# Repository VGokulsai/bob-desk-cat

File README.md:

# Bob, the desk cat

## The story

Bob is a cat that I drew in my sketchbook. Further up he went into the Wispr Flow hiring challenge as the main character that introduces my portfolio for that challenge.

After the completion of the challenge I moved on to Hack Club's Fallen, which is like a hard hackathon lasting 2 months. You build the project by hand: no AI, no bot can help you. You record your time, you get your XP, and stuff like that.

## Why I'm building him

Bob, the bot named Bob, is my cat, my sketchbook inspiration. Why am I building him? The reason that I'm building Bob is that I could feel less lonely while coding and while doing things.

## What Bob can do

What Bob can do is this: he has a screen, a mic, a speaker, and 3 servos. When we touch Bob he acts like an ordinary cat. He yawns, sleeps, and wakes up. His mic, speaker, and servos are all connected.

## The board

The board that I'm using is the ESP32-S3, 73 mm x 62.5 mm, 38 parts, and USB-C. These are the parts that are going to be on the board. As for the checks there are 0 ERC errors, 0 DRC errors, and 0 unconnected things.

## The hardest part

The next little bit of a bad story is that the USB D+ wire was a really tough one. That was the only single wire that I needed to connect in the entire schematic so that I could submit. As it was the last one, when I was going to connect it, there was no way. I had to reconnect so many wires, some of which I had to, and change the schematic design, replace parts, and stuff like that. It's been a really tough one until now.

## Cost and what's next

The cost of all the parts is ₹1,600 as I'm from India. What's next is that I'm going to be submitting the online version of Bob for now: the schematic, the PCB design, the doc, and the readme. Then I have to order all the hardware parts that I need to build him so that we can move on more quickly and probably go design.

## Files

- `hardware/` KiCad schematic and PCB
- `hardware/fab/` Gerbers for JLCPCB, BOM, parts positions, schematic PDF, board renders
- `bom.csv` shopping list

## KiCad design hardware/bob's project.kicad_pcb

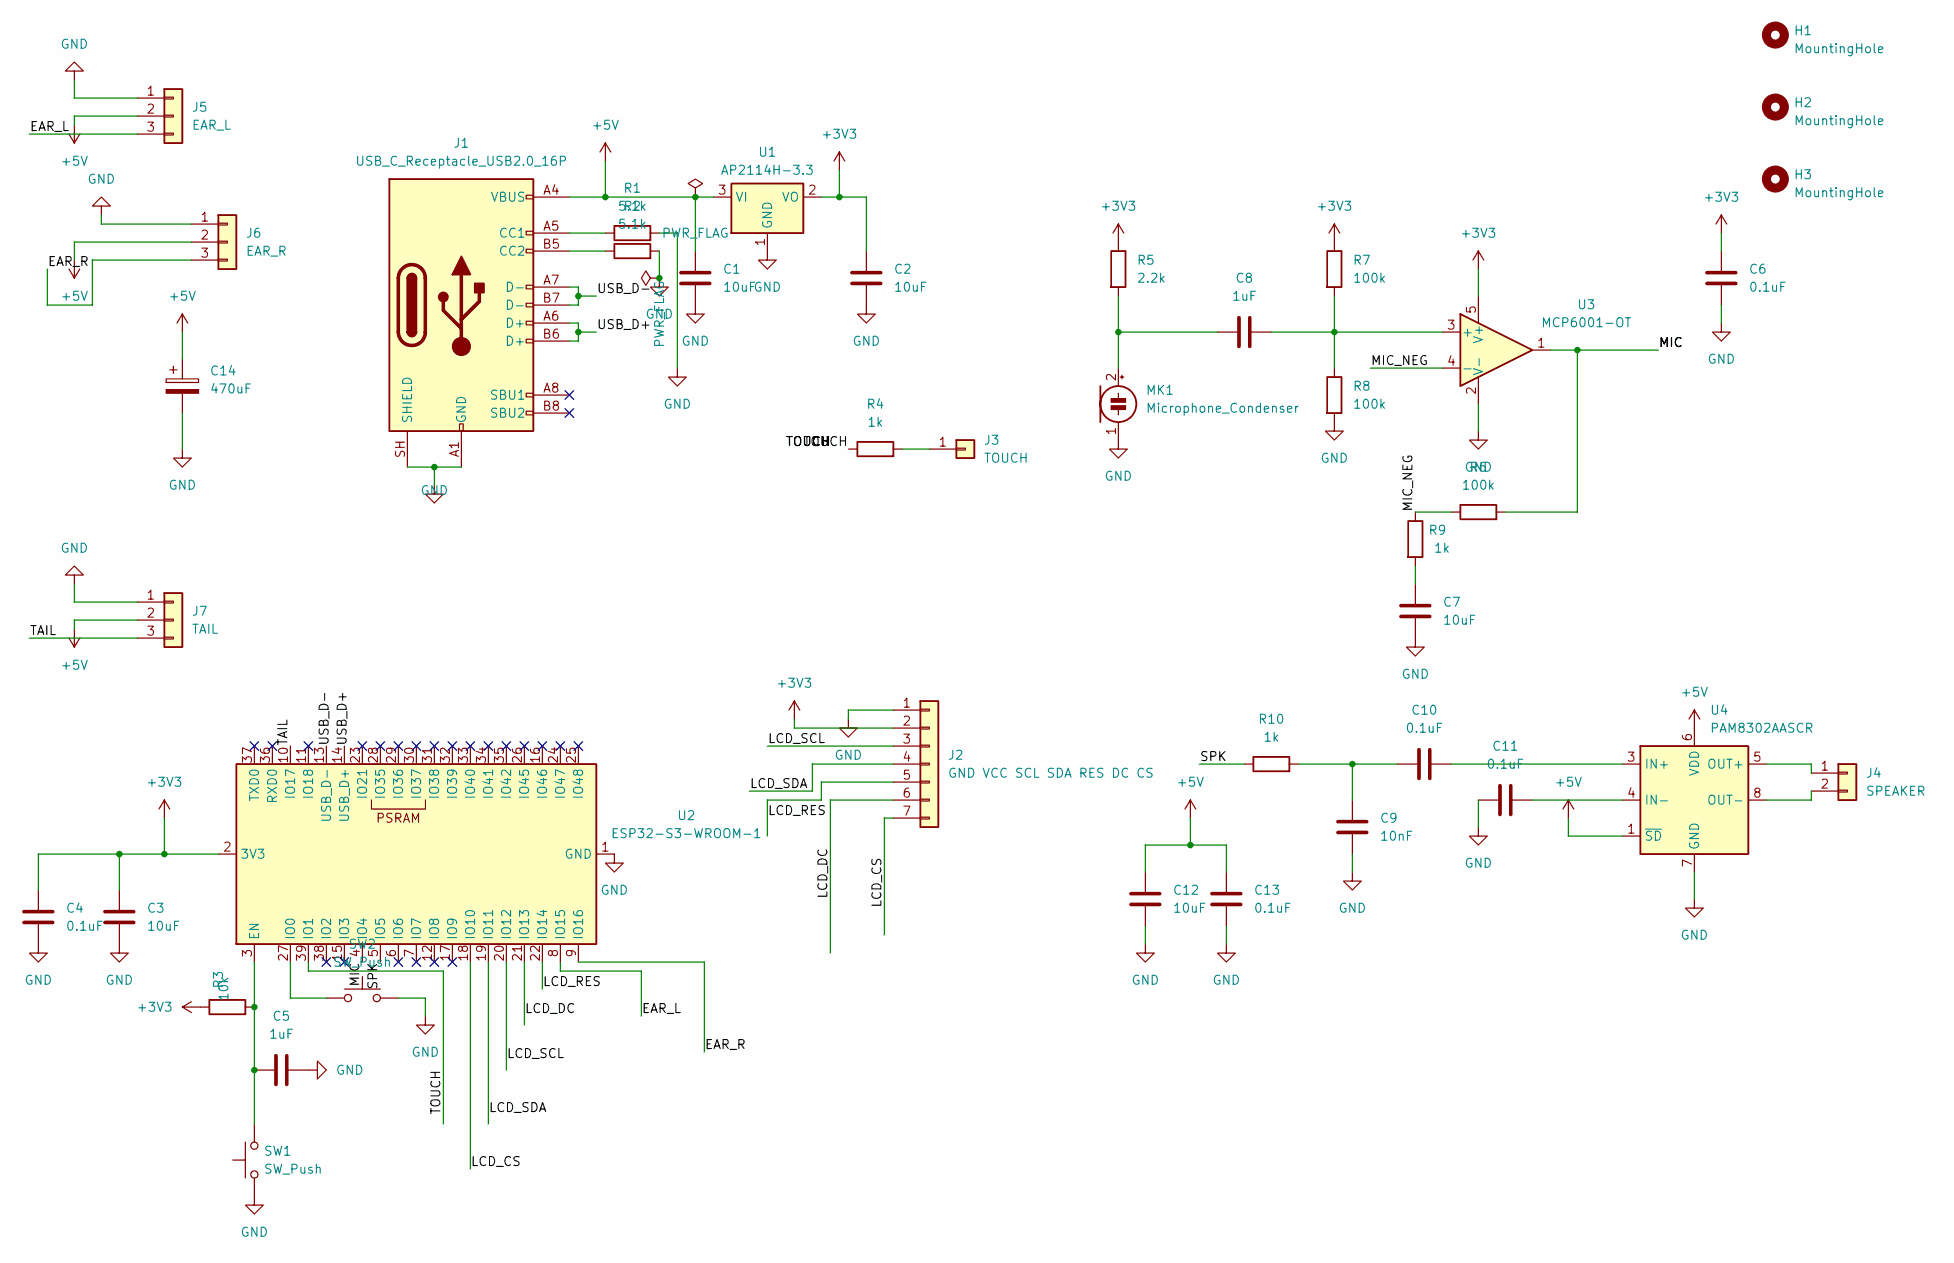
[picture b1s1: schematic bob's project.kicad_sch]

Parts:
C1, C2, C3, C7, C12: 10uF; C_0805_2012Metric_Pad1.18x1.45mm_HandSolder
C4, C6, C10, C11, C13: 0.1uF; C_0805_2012Metric_Pad1.18x1.45mm_HandSolder
C5, C8: 1uF; C_0805_2012Metric_Pad1.18x1.45mm_HandSolder
C9: 10nF; C_0805_2012Metric_Pad1.18x1.45mm_HandSolder
C14: 470uF; CP_Elec_8x10
H1, H2, H3: MountingHole; MountingHole_2.7mm_M2.5
J1: USB_C_Receptacle_USB2.0_16P; USB_C_Receptacle_HRO_TYPE-C-31-M-12
J2: GND VCC SCL SDA RES DC CS; PinHeader_1x07_P2.54mm_Vertical
J3: TOUCH; PinHeader_1x01_P2.54mm_Vertical
J4: SPEAKER; PinHeader_1x02_P2.54mm_Vertical
J5: EAR_L; PinHeader_1x03_P2.54mm_Vertical
J6: EAR_R; PinHeader_1x03_P2.54mm_Vertical
J7: TAIL; PinHeader_1x03_P2.54mm_Vertical
MK1: Microphone_Condenser; PinHeader_1x02_P2.54mm_Vertical
R1, R2: 5.1k; R_0805_2012Metric_Pad1.20x1.40mm_HandSolder
R3: 10k; R_0805_2012Metric_Pad1.20x1.40mm_HandSolder
R4, R9, R10: 1k; R_0805_2012Metric_Pad1.20x1.40mm_HandSolder
R5: 2.2k; R_0805_2012Metric_Pad1.20x1.40mm_HandSolder
R6, R7, R8: 100k; R_0805_2012Metric_Pad1.20x1.40mm_HandSolder
SW1, SW2: SW_Push; SW_PUSH_6mm
U1: AP2114H-3.3; SOT-223-3_TabPin2
U2: ESP32-S3-WROOM-1
U3: MCP6001-OT; SOT-23-5
U4: PAM8302AASCR; MSOP-8_3x3mm_P0.65mm

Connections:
+3V3: C2.1, C3.1, C4.1, C6.1, J2.2, R3.1, R5.1, R7.1, U1.2 (VO), U2.2 (3V3), U3.5 (V+)
+5V: C1.1, C12.1, C13.1, C14.1, J1.A4 (VBUS), J1.A9 (VBUS), J1.B4 (VBUS), J1.B9 (VBUS), J5.2, J6.2, J7.2, U1.3 (VI), U4.1 (~SD), U4.6 (VDD)
/EAR_L: J5.3, U2.8 (IO15)
/EAR_R: J6.3, U2.9 (IO16)
/LCD_CS: J2.7, U2.18 (IO10)
/LCD_DC: J2.6, U2.21 (IO13)
/LCD_RES: J2.5, U2.22 (IO14)
/LCD_SCL: J2.3, U2.20 (IO12)
/LCD_SDA: J2.4, U2.19 (IO11)
/MIC: R6.2, U2.4 (IO4), U3.1
/MIC_NEG: R6.1, R9.1, U3.4 (-)
/SPK: R10.1, U2.5 (IO5)
/TAIL: J7.3, U2.10 (IO17)
/TOUCH: R4.1, U2.39 (IO1)
/USB_D+: J1.A6 (D+), J1.B6 (D+), U2.14 (USB_D+)
/USB_D-: J1.A7 (D-), J1.B7 (D-), U2.13 (USB_D-)
GND: C1.2, C2.2, C3.2, C4.2, C5.2, C6.2, C7.2, C9.2, C11.1, C12.2, C13.2, C14.2, J1.A1 (GND), J1.A12 (GND), J1.B1 (GND), J1.B12 (GND), J1.SH (SHIELD), J2.1, J5.1, J6.1, J7.1, MK1.1 (-), R1.2, R2.2, R8.2, SW1.1, SW2.2, U1.1 (GND), U2.1 (GND), U2.40 (GND), U2.41 (GND), U3.2 (V-), U4.7 (GND)
unnamed: C7.1, R9.2
unnamed: C9.1, C10.1, R10.2
unnamed: J1.A5 (CC1), R1.1
unnamed: J1.B5 (CC2), R2.1
unnamed: J3.1 (Pin_1_1), R4.2
unnamed: J4.1, U4.5 (OUT+)
unnamed: J4.2, U4.8 (OUT-)
unnamed: C8.1, MK1.2 (+), R5.2
unnamed: C5.1, R3.2, SW1.2, U2.3 (EN)
unnamed: SW2.1, U2.27 (IO0)
unnamed: C8.2, R7.2, R8.1, U3.3 (+)
unnamed: C10.2, U4.3 (IN+)
unnamed: C11.2, U4.4 (IN-)

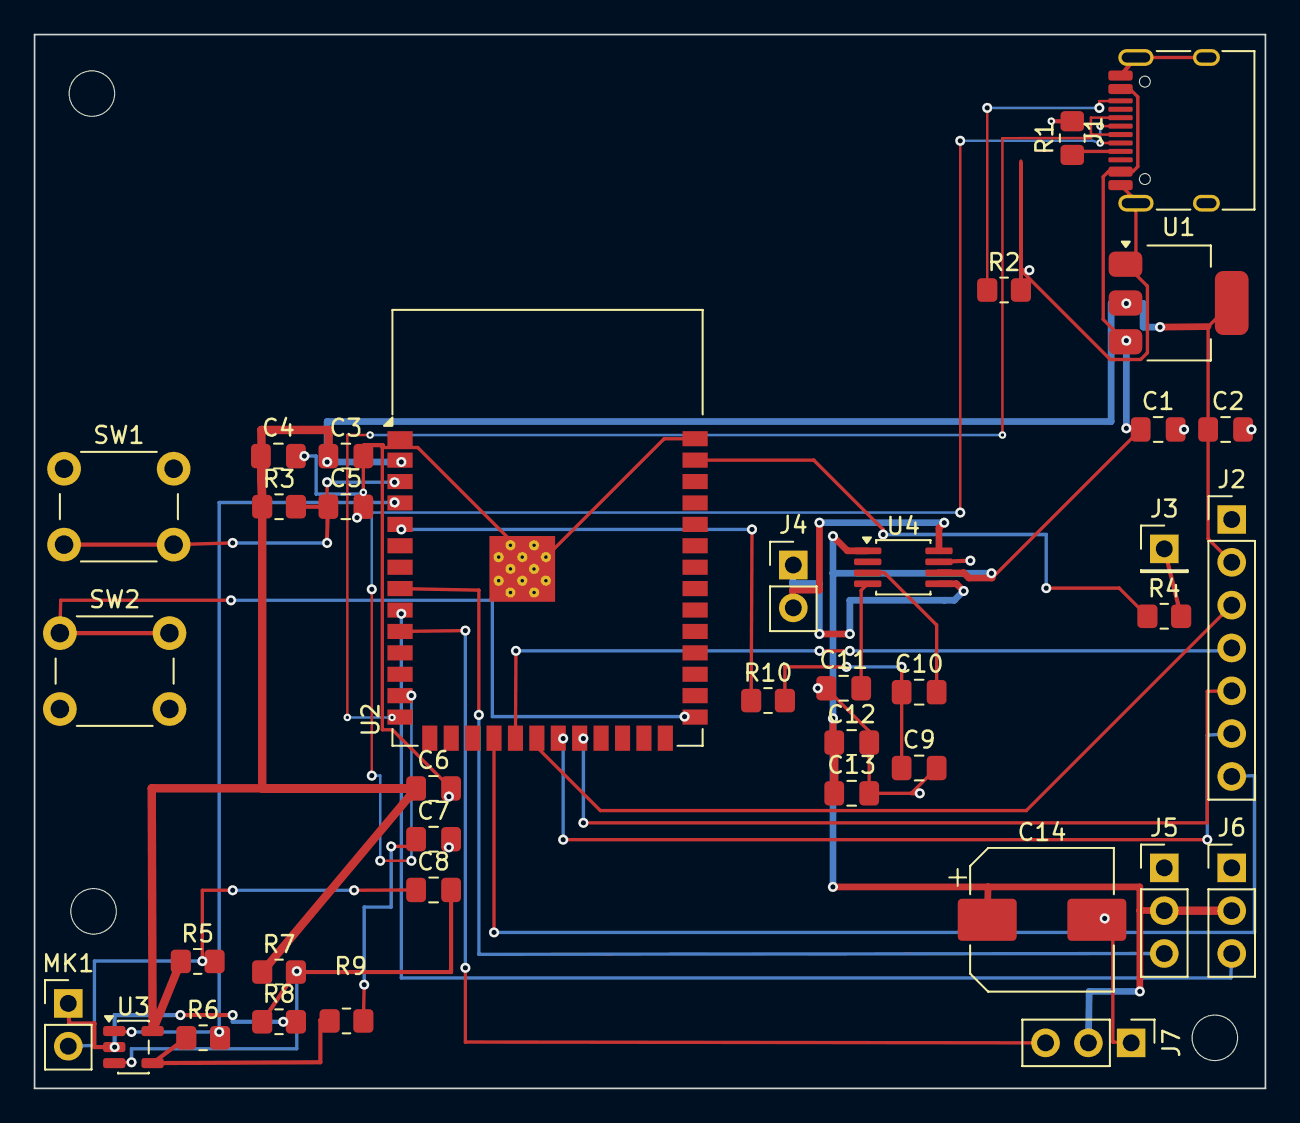
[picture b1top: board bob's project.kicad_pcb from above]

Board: 2 copper layers, 73.0 x 62.5 mm, 41 parts (0 on the bottom side), 30 nets.

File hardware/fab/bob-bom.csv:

"Reference","Value","Footprint","Quantity"
"C1-C3,C7,C12","10uF","Capacitor_SMD:C_0805_2012Metric_Pad1.18x1.45mm_HandSolder","5"
"C4,C6,C10,C11,C13","0.1uF","Capacitor_SMD:C_0805_2012Metric_Pad1.18x1.45mm_HandSolder","5"
"C5,C8","1uF","Capacitor_SMD:C_0805_2012Metric_Pad1.18x1.45mm_HandSolder","2"
"C9","10nF","Capacitor_SMD:C_0805_2012Metric_Pad1.18x1.45mm_HandSolder","1"
"C14","470uF","Capacitor_SMD:CP_Elec_8x10","1"
"J1","USB_C_Receptacle_USB2.0_16P","Connector_USB:USB_C_Receptacle_HRO_TYPE-C-31-M-12","1"
"J2","GND VCC SCL SDA RES DC CS","Connector_PinHeader_2.54mm:PinHeader_1x07_P2.54mm_Vertical","1"
"J3","TOUCH","Connector_PinHeader_2.54mm:PinHeader_1x01_P2.54mm_Vertical","1"
"J4","SPEAKER","Connector_PinHeader_2.54mm:PinHeader_1x02_P2.54mm_Vertical","1"
"J5","EAR_L","Connector_PinHeader_2.54mm:PinHeader_1x03_P2.54mm_Vertical","1"
"J6","EAR_R","Connector_PinHeader_2.54mm:PinHeader_1x03_P2.54mm_Vertical","1"
"J7","TAIL","Connector_PinHeader_2.54mm:PinHeader_1x03_P2.54mm_Vertical","1"
"MK1","Microphone_Condenser","Connector_PinHeader_2.54mm:PinHeader_1x02_P2.54mm_Vertical","1"
"R1,R2","5.1k","Resistor_SMD:R_0805_2012Metric_Pad1.20x1.40mm_HandSolder","2"
"R3","10k","Resistor_SMD:R_0805_2012Metric_Pad1.20x1.40mm_HandSolder","1"
"R4,R9,R10","1k","Resistor_SMD:R_0805_2012Metric_Pad1.20x1.40mm_HandSolder","3"
"R5","2.2k","Resistor_SMD:R_0805_2012Metric_Pad1.20x1.40mm_HandSolder","1"
"R6-R8","100k","Resistor_SMD:R_0805_2012Metric_Pad1.20x1.40mm_HandSolder","3"
"SW1,SW2","SW_Push","Button_Switch_THT:SW_PUSH_6mm","2"
"U1","AP2114H-3.3","Package_TO_SOT_SMD:SOT-223-3_TabPin2","1"
"U2","ESP32-S3-WROOM-1","RF_Module:ESP32-S3-WROOM-1","1"
"U3","MCP6001-OT","Package_TO_SOT_SMD:SOT-23-5","1"
"U4","PAM8302AASCR","Package_SO:MSOP-8_3x3mm_P0.65mm","1"
